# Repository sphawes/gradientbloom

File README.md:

# GradientBloom
GradientBloom is an Open Source version of [Spectrabloom](https://lorre-mill.com/spectrabloom).

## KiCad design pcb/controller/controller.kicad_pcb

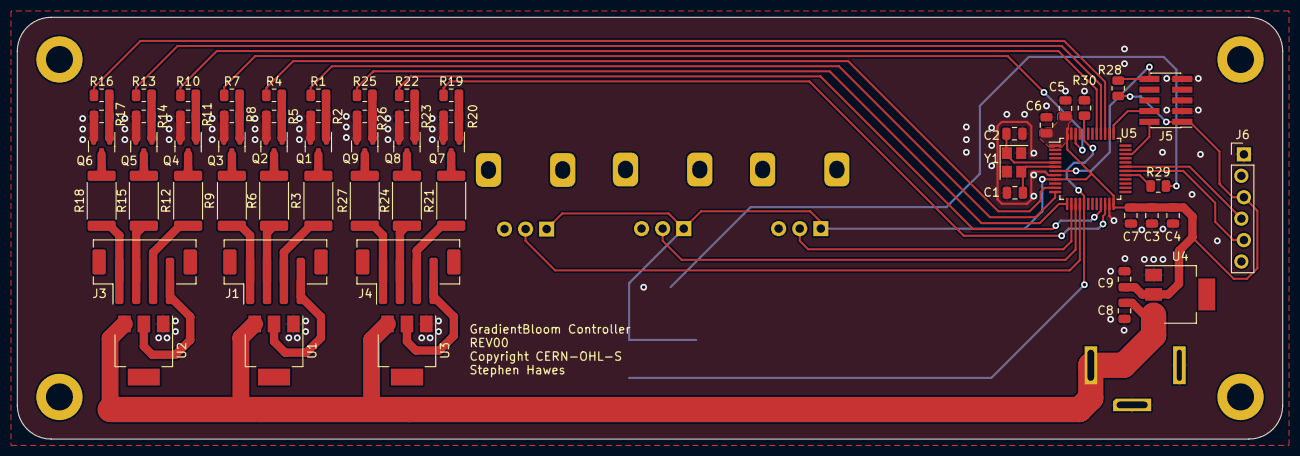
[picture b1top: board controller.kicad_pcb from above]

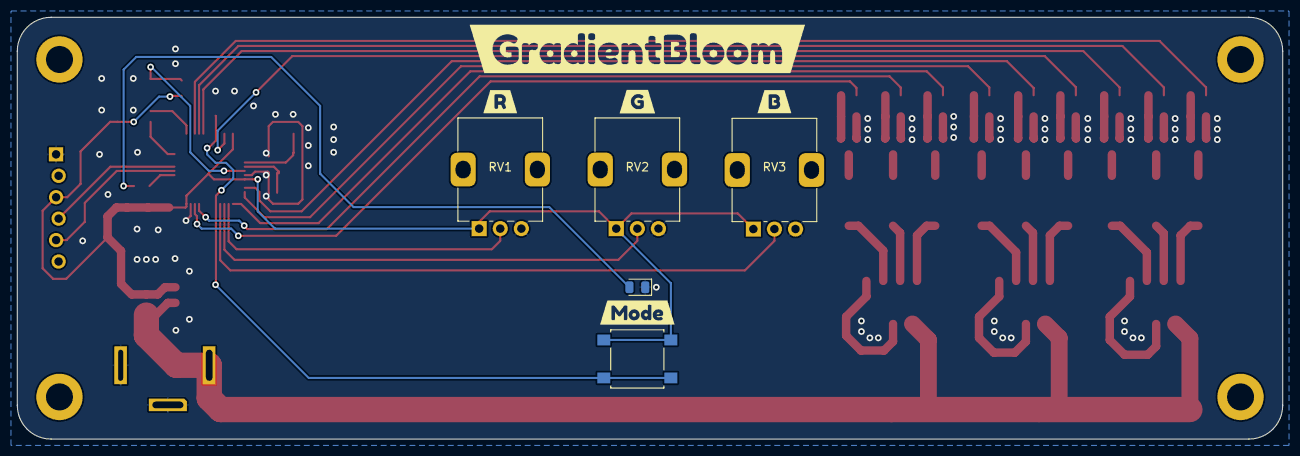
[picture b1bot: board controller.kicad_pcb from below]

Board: 2 copper layers, 150.0 x 50.0 mm, 74 parts (11 on the bottom side), 55 nets.

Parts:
C1, C2: 15pF; C_0805_2012Metric
C3, C4, C5: 100nF; C_0805_2012Metric
C6, C7: 4.7uF; C_0805_2012Metric
C8, C9: 10uF; C_0805_2012Metric
D1: LED; LED_0805_2012Metric
H1, H2, H3, H4: MountingHole; MountingHole_3.2mm_M3_ISO14580_Pad
J1, J3, J4: LED0; JST_PH_B4B-PH-SM4-TB_1x04-1MP_P2.00mm_Vertical
J2: Barrel_Jack_MountingPin; DC-012A-20A
J5: Conn_ARM_JTAG_SWD_10; PinHeader_2x05_P1.27mm_Vertical_SMD
J6: PROGRAMMING_HEADER; UART_FRICTION_FIT
Q1, Q2, Q3, Q4, Q5, Q6, Q7, Q8, Q9: AO3400A; SOT-23
R1, R4, R7, R10, R13, R16, R19, R22, R25: 120R; R_0805_2012Metric
R2, R5, R8, R11, R14, R17, R20, R23, R26: 10k; R_0805_2012Metric
R3, R6, R9, R12, R15, R18, R21, R24, R27: 15R; R_2512_6332Metric
R28, R30: 10K; R_0805_2012Metric
R29: 220R; R_0805_2012Metric
RV1: R_POT; Potentiometer_Alps_RK09K_Single_Vertical
RV2: G_POT; Potentiometer_Alps_RK09K_Single_Vertical
RV3: B_POT; Potentiometer_Alps_RK09K_Single_Vertical
SW1: MODE/BOOT; SW_SPST_B3S-1000
U1, U2, U3: AZ1117-5.0; SOT-223
U4: AZ1117-3.3; SOT-223
U5: STM32F031C6Tx; LQFP-48_7x7mm_P0.5mm
Y1: 8MHz; Crystal_SMD_3225-4Pin_3.2x2.5mm
kibuzzard-64A36E8B: G***; kibuzzard-64A36E8B
kibuzzard-64A36F3A: G***; kibuzzard-64A36F3A
kibuzzard-64A36F4E: G***; kibuzzard-64A36F4E
kibuzzard-64A36F5D: G***; kibuzzard-64A36F5D
kibuzzard-64A36FD2: G***; kibuzzard-64A36FD2

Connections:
+3V3: C3.1, C4.1, C5.1, C6.1, C7.1, C9.1, J5.1 (VTref), J6.3, R28.1, RV1.1, RV2.1, RV3.1, SW1.1, U4.2 (VO), U5.1 (VBAT), U5.9 (VDDA), U5.24 (VDD), U5.48 (VDD)
+12V: C8.1, J2.1, U1.3 (VI), U2.3 (VI), U3.3 (VI), U4.3 (VI)
/B_POT: RV3.2, U5.16 (PA6)
/G_POT: RV2.2, U5.15 (PA5)
/LED: R29.1, U5.29 (PA8)
/LED0/B_OUT: J3.1, R18.1
/LED0/G_OUT: J3.2, R15.1
/LED0/R_OUT: J3.3, R12.1
/LED0_B: R16.1, U5.39 (PB3)
/LED0_G: R13.1, U5.40 (PB4)
/LED0_R: R10.1, U5.41 (PB5)
/LED1/B_OUT: J1.1, R9.1
/LED1/G_OUT: J1.2, R6.1
/LED1/R_OUT: J1.3, R3.1
/LED1_B: R7.1, U5.46 (PB9)
/LED1_G: R4.1, U5.11 (PA1)
/LED1_R: R1.1, U5.12 (PA2)
/LED2/B_OUT: J4.1, R27.1
/LED2/G_OUT: J4.2, R24.1
/LED2/R_OUT: J4.3, R21.1
/LED2_B: R25.1, U5.13 (PA3)
/LED2_G: R22.1, U5.21 (PB10)
/LED2_R: R19.1, U5.22 (PB11)
/R_POT: RV1.2, U5.14 (PA4)
BOOT0: R30.1, SW1.2, U5.17 (PA7), U5.44 (BOOT0)
GND: C1.2, C2.1, C3.2, C4.2, C5.2, C6.2, C7.2, C8.2, C9.2, D1.1 (K), J2.2, J5.3 (GND), J5.5 (GND), J5.9 (GNDDetect), J6.1, Q1.2 (S), Q2.2 (S), Q3.2 (S), Q4.2 (S), Q5.2 (S), Q6.2 (S), Q7.2 (S), Q8.2 (S), Q9.2 (S), R2.2, R5.2, R8.2, R11.2, R14.2, R17.2, R20.2, R23.2, R26.2, R30.2, RV1.3, RV2.3, RV3.3, U1.1 (GND), U2.1 (GND), U3.1 (GND), U4.1 (GND), U5.8 (VSSA), U5.23 (VSS), U5.47 (VSS), Y1.2, Y1.4
MCU_RX: J6.4, U5.31 (PA10)
MCU_TX: J6.5, U5.30 (PA9)
unnamed: D1.2 (A), R29.2
unnamed: J1.4, U1.2 (VO)
unnamed: J3.4, U2.2 (VO)
unnamed: J4.4, U3.2 (VO)
unnamed: Q1.3 (D), R3.2
unnamed: Q1.1 (G), R1.2, R2.1
unnamed: Q2.3 (D), R6.2
unnamed: Q2.1 (G), R4.2, R5.1
unnamed: Q3.3 (D), R9.2
unnamed: Q3.1 (G), R7.2, R8.1
unnamed: Q4.3 (D), R12.2
unnamed: Q4.1 (G), R10.2, R11.1
unnamed: Q5.3 (D), R15.2
unnamed: Q5.1 (G), R13.2, R14.1
unnamed: Q6.3 (D), R18.2
unnamed: Q6.1 (G), R16.2, R17.1
unnamed: Q7.3 (D), R21.2
unnamed: Q7.1 (G), R19.2, R20.1
unnamed: Q8.3 (D), R24.2
unnamed: Q8.1 (G), R22.2, R23.1
unnamed: Q9.3 (D), R27.2
unnamed: Q9.1 (G), R25.2, R26.1
OSC_IN: C2.2, U5.5 (PF0), Y1.1
OSC_OUT: C1.1, U5.6 (PF1), Y1.3
RESET: J5.10 (~RESET), R28.2, U5.7 (NRST)
SWCLK: J5.4 (SWDCLK/TCK), U5.37 (PA14)
SWDIO: J5.2 (SWDIO/TMS), U5.34 (PA13)

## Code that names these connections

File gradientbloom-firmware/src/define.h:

#define R_POT PA4
#define G_POT PA5
#define B_POT PA6

#define MODE PA7
#define LED PA8

#define LED0_R PB5  //TIM3_CH2
#define LED0_G PB4  //TIM3_CH1
#define LED0_B PB3  //TIM2_CH2

#define LED1_R PA2  //TIM2_CH3
#define LED1_G PA11 //TIM1_CH4 
#define LED1_B PA0  //TIM2_CH1

#define LED2_R PB0  //TIM3_CH3
#define LED2_G PB1  //TIM3_CH4
#define LED2_B PA3  //TIM2_CH4

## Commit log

2023-07-04 initial commit with rev00 of the pcb and base cad
2023-07-04 adds a bit to readme
2023-07-08 adds ds store to git ignore
2023-07-08 adds prelim firmware
2023-07-08 pcb tweaks
2023-07-08 removed ds store
2023-08-01 fixes pins for pwm and timers because im mush and didnt think aobut it when routing
2026-01-11 updates firmware

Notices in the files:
pcb/controller/controller.kicad_pcb:
Copyright CERN-OHL-S
